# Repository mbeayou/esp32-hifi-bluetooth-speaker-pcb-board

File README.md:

# ESP32 HiFi Bluetooth Speaker PCB Board

This project showcases the design and assembly of a **HiFi Bluetooth speaker PCB board** based on the ESP32.  
It includes PCB layer visualization, the assembled board, and BLE schematics for reference.

## 📐 PCB Layers

## 🔧 Assembled PCB

## 📊 Schematics (BLE)

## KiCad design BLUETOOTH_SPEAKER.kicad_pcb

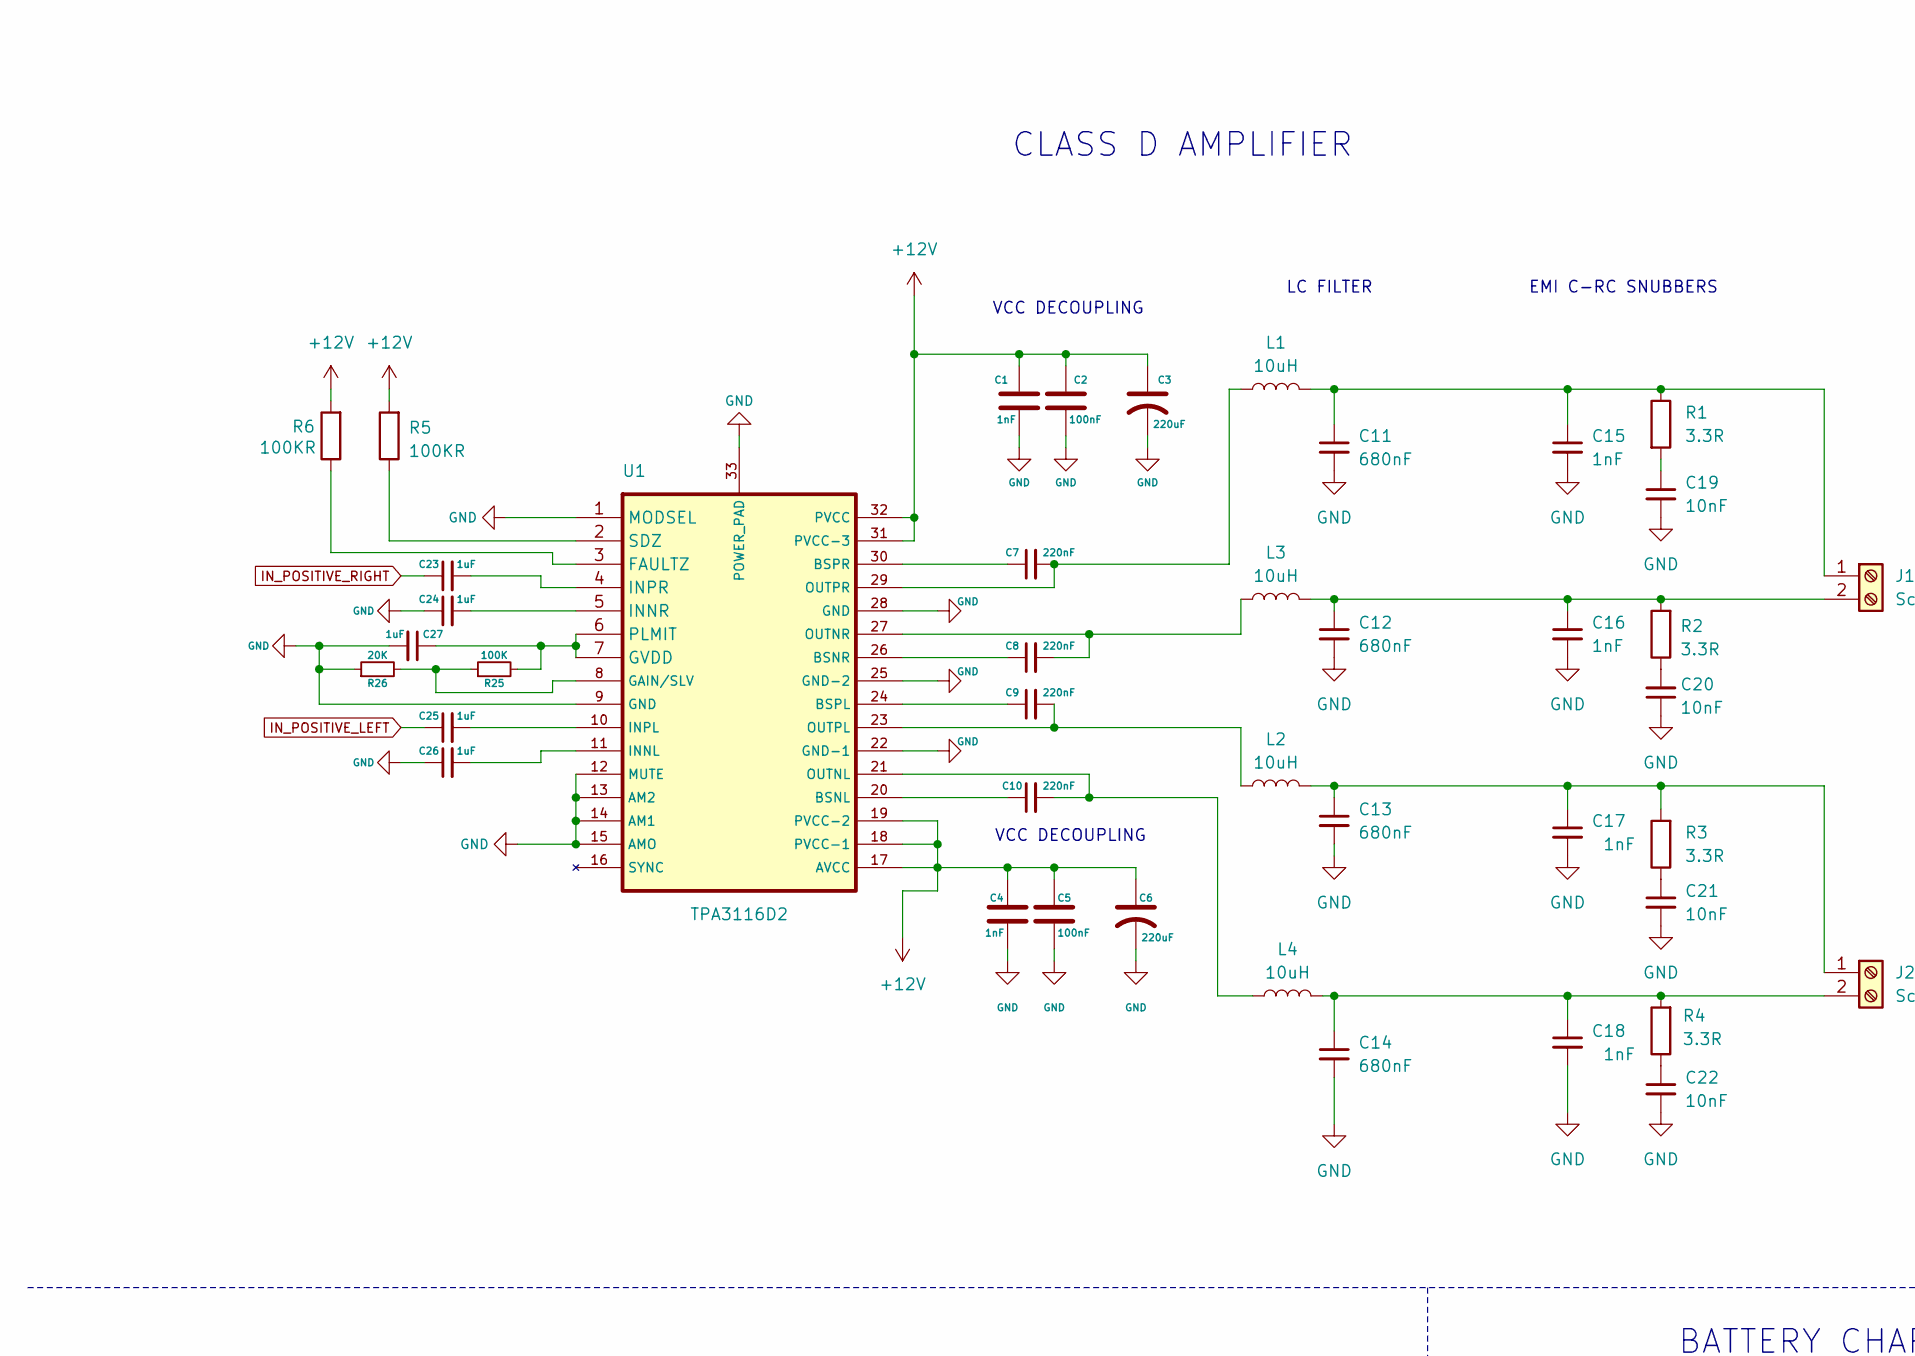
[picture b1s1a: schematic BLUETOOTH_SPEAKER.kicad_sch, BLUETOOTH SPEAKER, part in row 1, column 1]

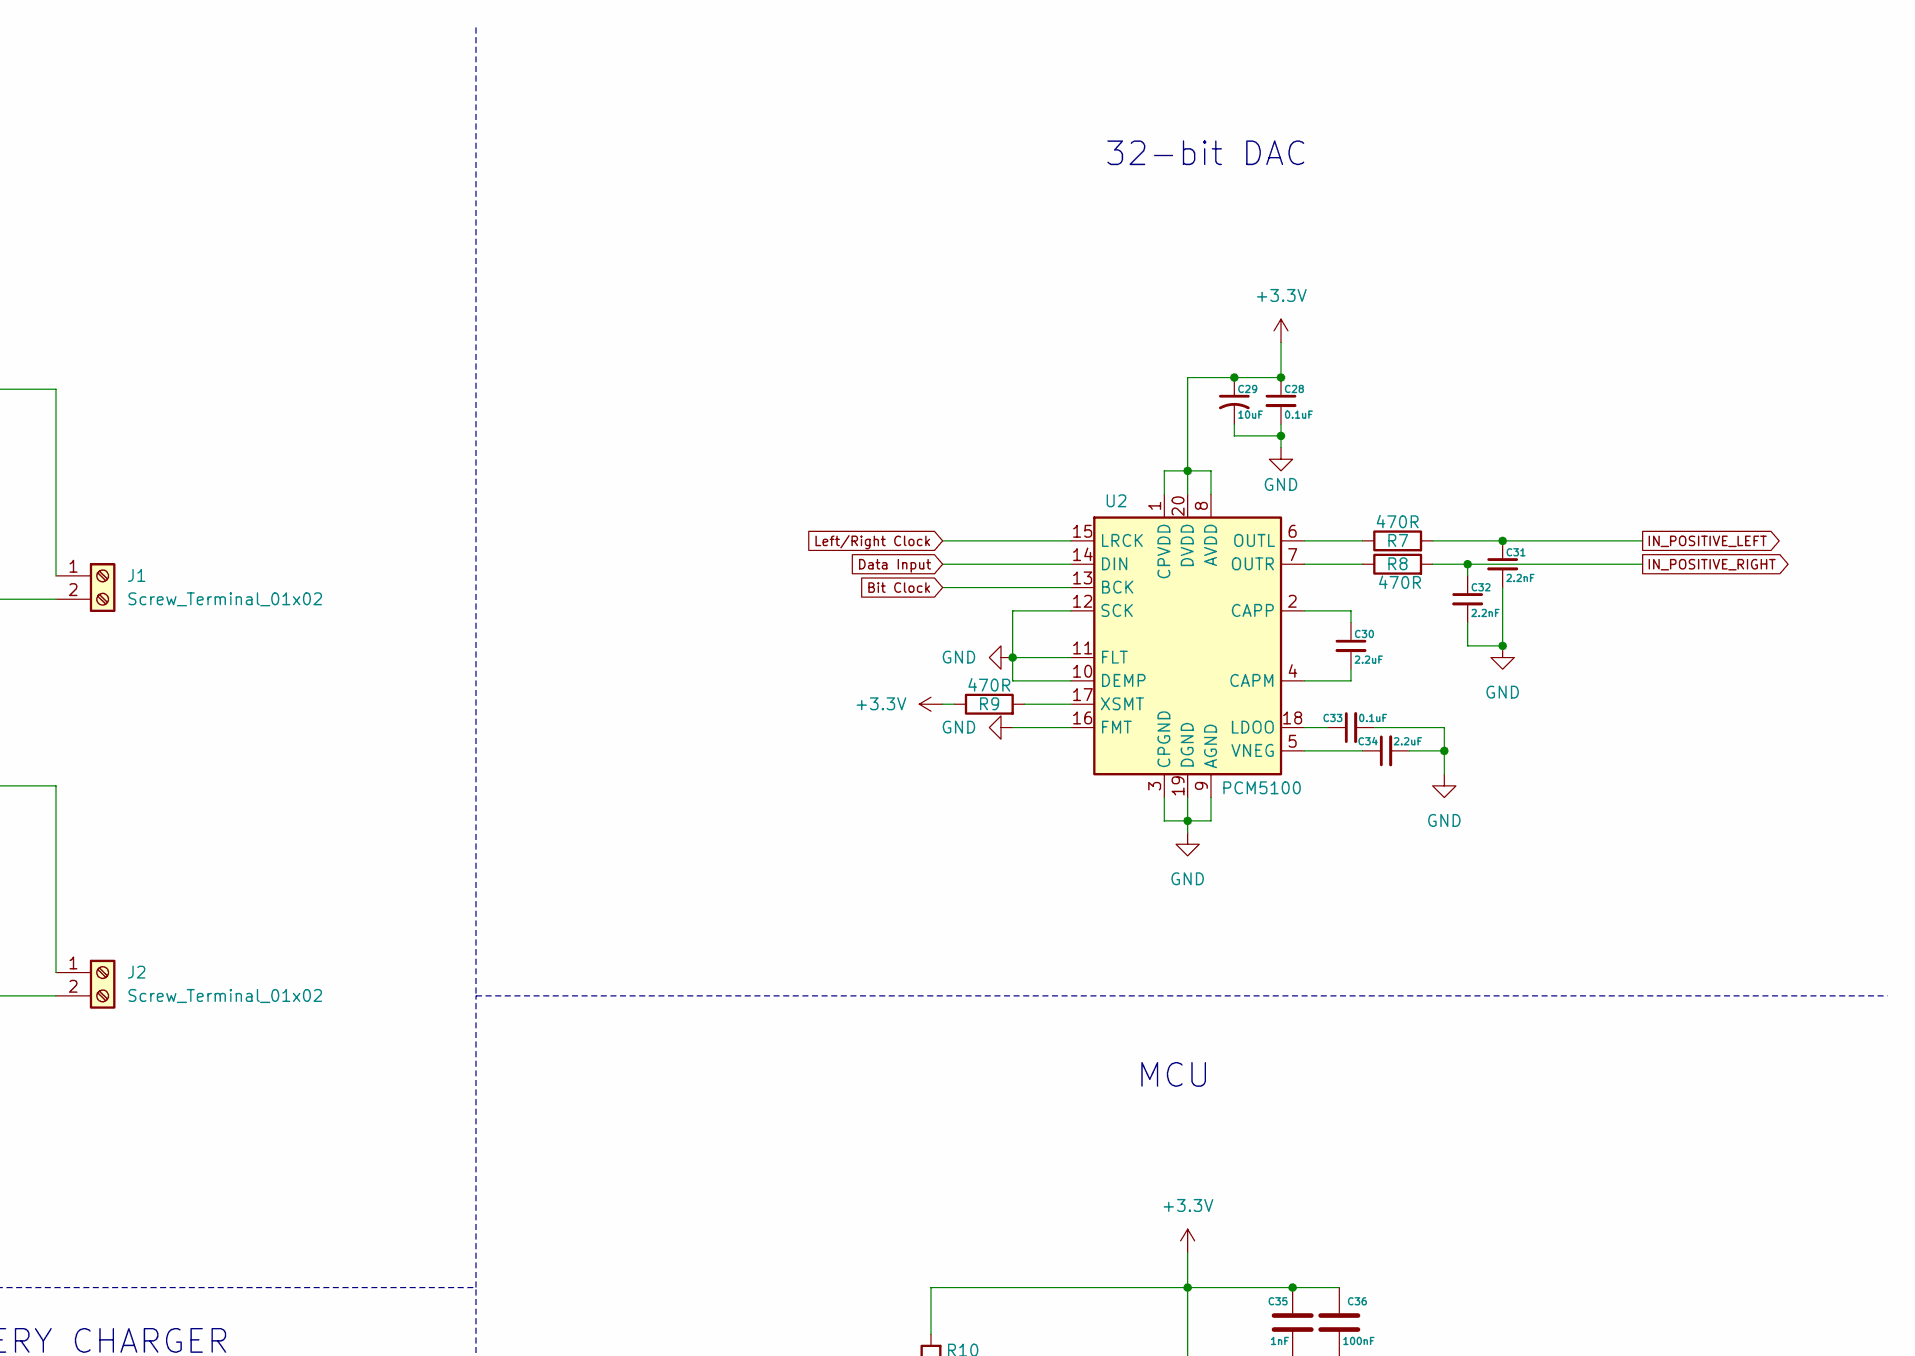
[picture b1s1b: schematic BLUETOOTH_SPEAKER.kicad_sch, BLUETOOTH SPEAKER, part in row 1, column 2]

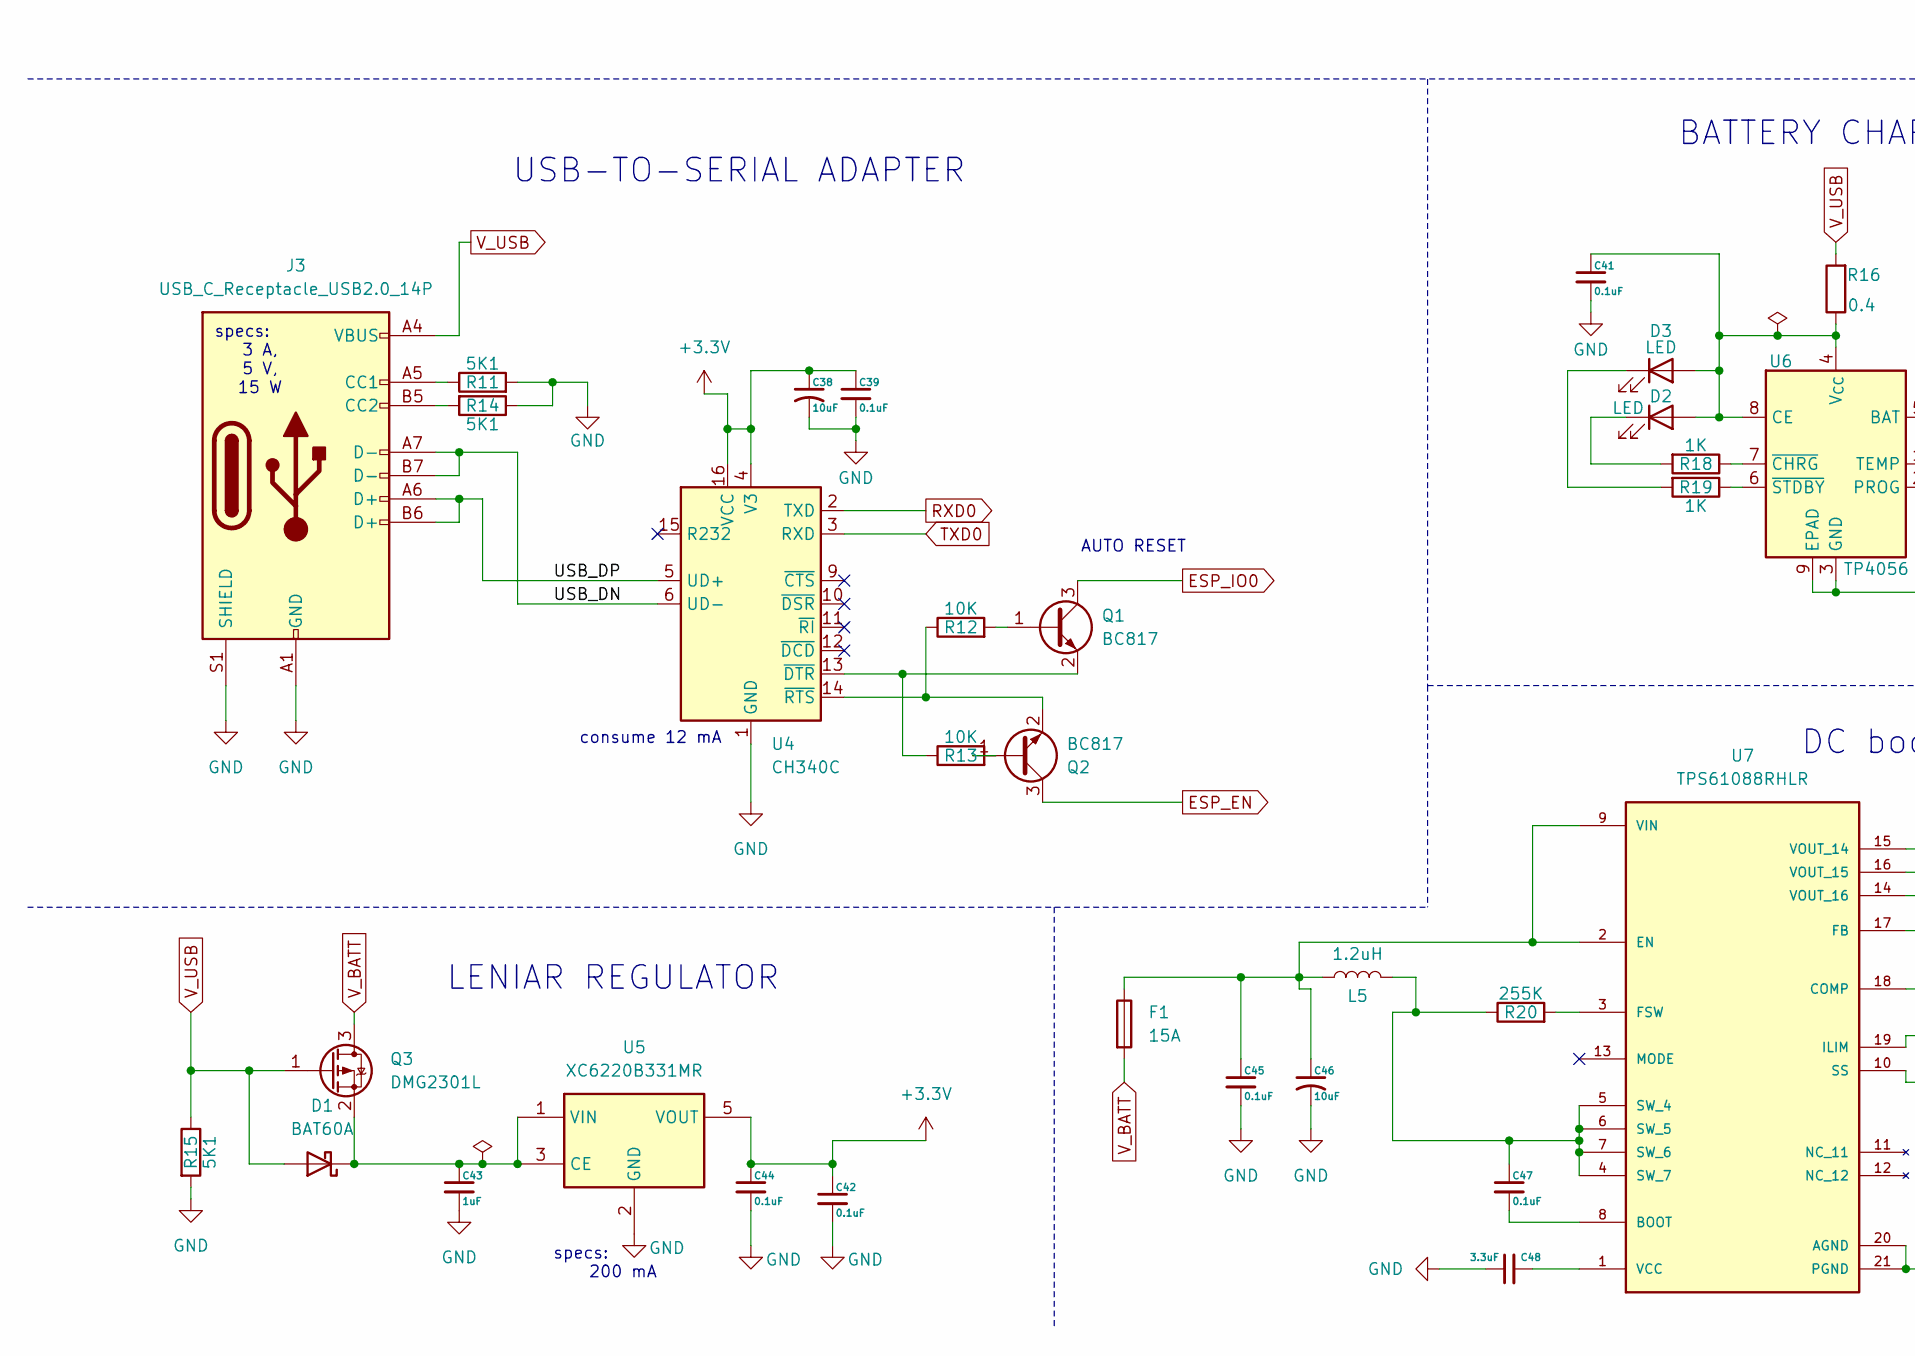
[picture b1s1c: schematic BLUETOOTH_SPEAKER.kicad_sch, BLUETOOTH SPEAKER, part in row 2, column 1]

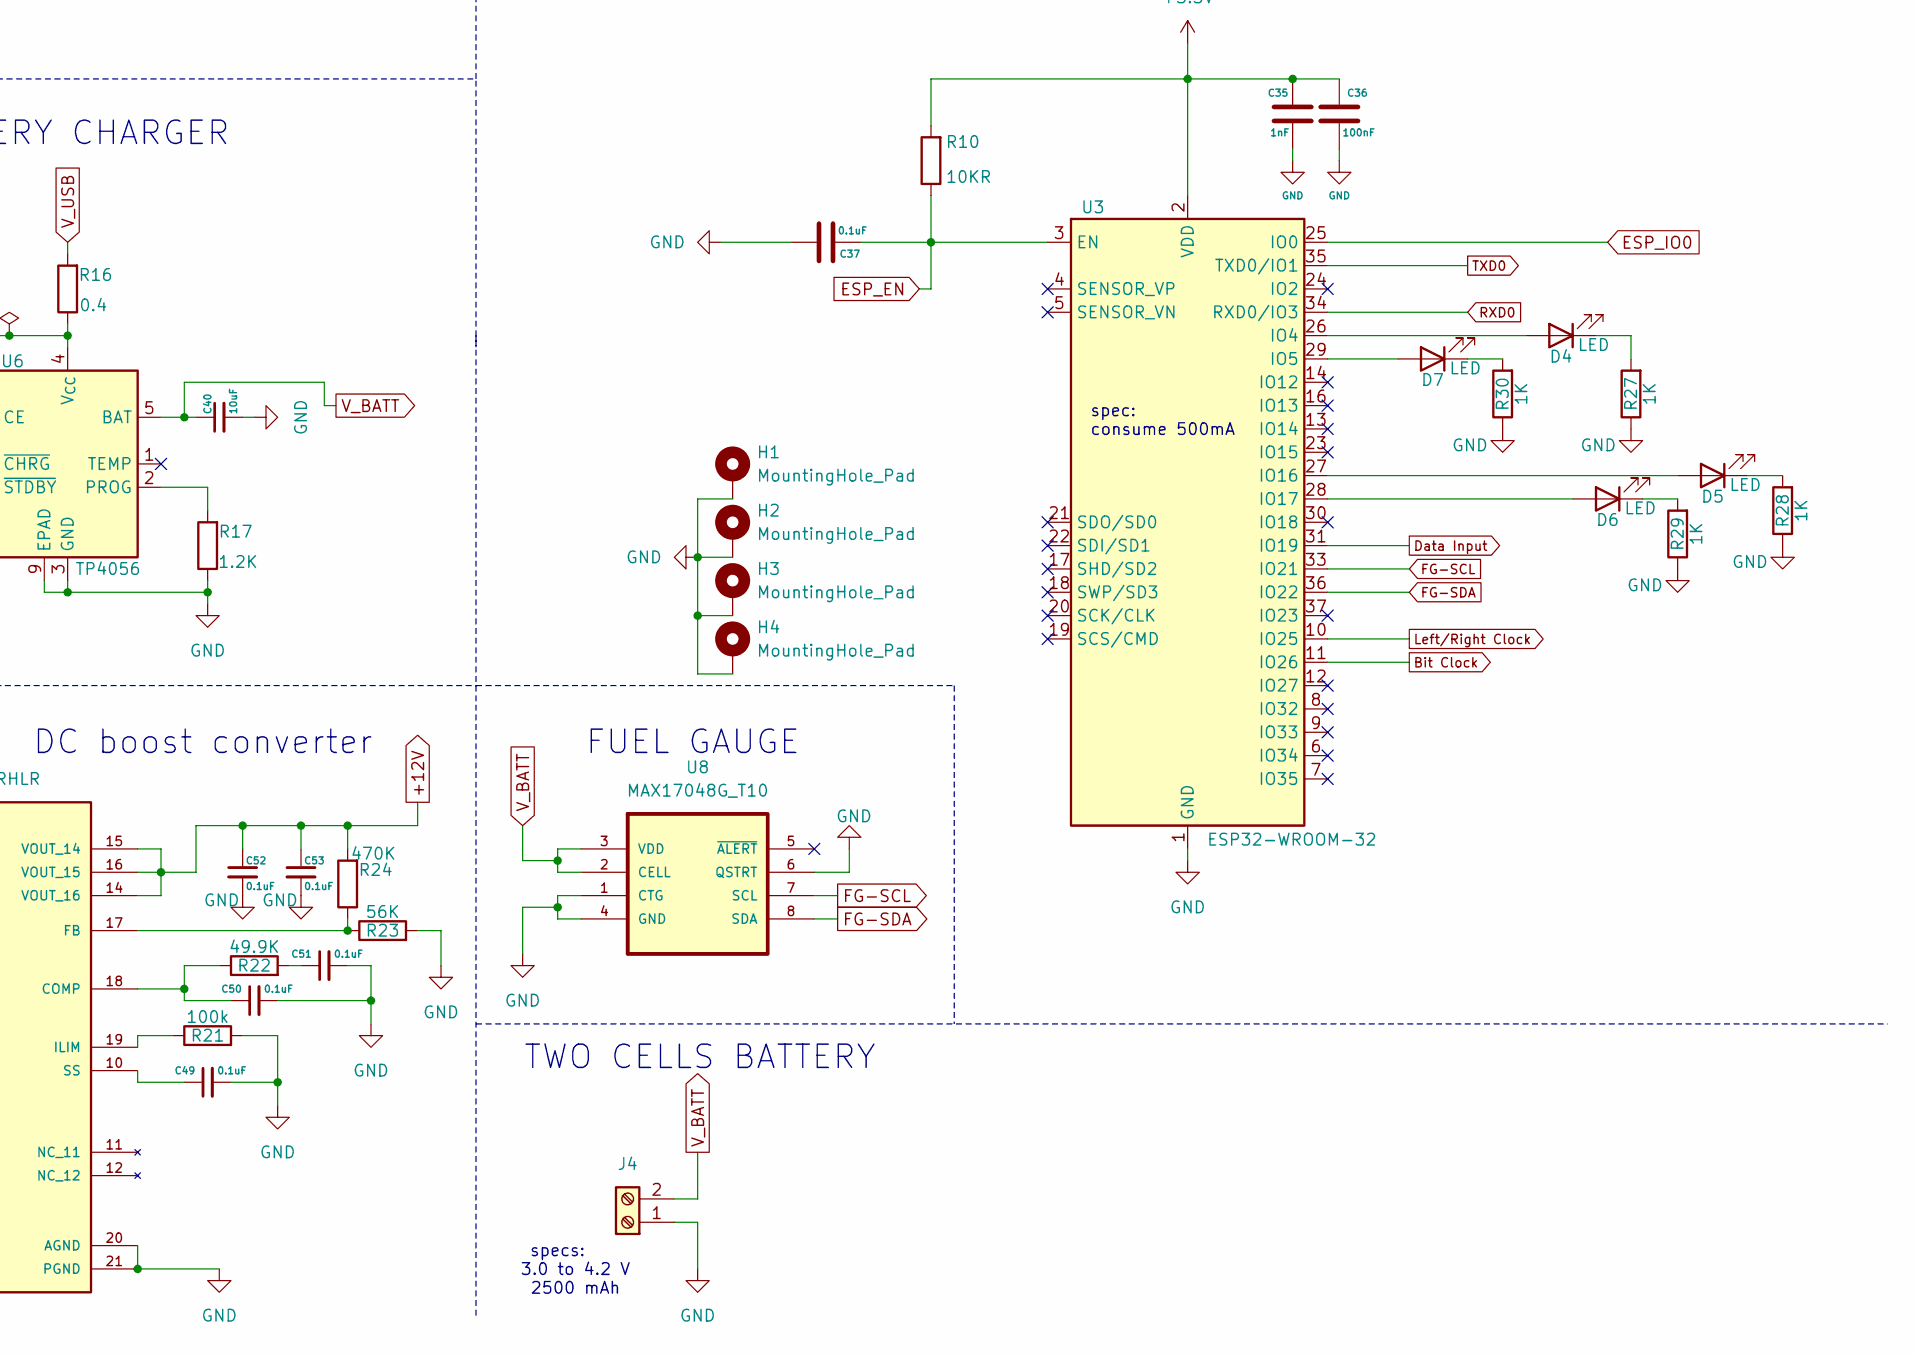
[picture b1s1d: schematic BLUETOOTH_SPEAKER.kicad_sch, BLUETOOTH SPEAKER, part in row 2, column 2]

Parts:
C1, C4, C15, C16, C17, C18, C35: 1nF; C_0603_1608Metric_Pad1.08x0.95mm_HandSolder
C2, C5, C36: 100nF; C_0805_2012Metric_Pad1.18x1.45mm_HandSolder
C3, C6: 220uF; C_1210_3225Metric_Pad1.33x2.70mm_HandSolder
C7, C8, C9, C10: 220nF; C_0805_2012Metric_Pad1.18x1.45mm_HandSolder
C11, C12, C13, C14: 680nF; C_0805_2012Metric_Pad1.18x1.45mm_HandSolder
C19, C20, C21, C22: 10nF; C_0603_1608Metric_Pad1.08x0.95mm_HandSolder
C23, C24, C25, C26, C43: 1uF; C_0805_2012Metric_Pad1.18x1.45mm_HandSolder
C27: 1uF; C_1206_3216Metric
C28, C33, C37, C39, C41, C42, C44, C45, C47, C49, C50, C51, C52, C53: 0.1uF; C_0805_2012Metric_Pad1.18x1.45mm_HandSolder
C29: 10uF; C_1206_3216Metric_Pad1.33x1.80mm_HandSolder
C30, C34: 2.2uF; C_0805_2012Metric_Pad1.18x1.45mm_HandSolder
C31, C32: 2.2nF; C_0603_1608Metric_Pad1.08x0.95mm_HandSolder
C38, C40, C46: 10uF; C_1210_3225Metric_Pad1.33x2.70mm_HandSolder
C48: 3.3uF; C_0805_2012Metric_Pad1.18x1.45mm_HandSolder
D1: BAT60A; D_SOD-323
D2, D3, D4, D5, D6, D7: LED; LED_1210_3225Metric_Pad1.42x2.65mm_HandSolder
F1: 15A; Fuseholder_Cylinder-6.3x32mm_Schurter_0031-8002_Horizontal_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
H1, H2, H3, H4: MountingHole_Pad; MountingHole_2.2mm_M2_Pad_Via
J1, J2: Screw_Terminal_01x02; JST_XH_S2B-XH-A-1_1x02_P2.50mm_Horizontal
J3: USB_C_Receptacle_USB2.0_14P; USB_C_Receptacle_Palconn_UTC16-G
J4: Screw_Terminal_01x02; JST_PH_B2B-PH-K_1x02_P2.00mm_Vertical
L1, L2, L3, L4: 10uH; WE-PD_1260
L5: 1.2uH; WE-PD_1260
Q1, Q2: BC817; SOT-23
Q3: DMG2301L; SOT-23
R1, R2, R3, R4: 3.3R; R_0603_1608Metric_Pad0.98x0.95mm_HandSolder
R5, R6: 100KR; R_1210_3225Metric_Pad1.30x2.65mm_HandSolder
R7, R8, R9: 470R; R_0805_2012Metric_Pad1.20x1.40mm_HandSolder
R10: 10KR; R_1210_3225Metric_Pad1.30x2.65mm_HandSolder
R11, R14, R15: 5K1; R_0805_2012Metric_Pad1.20x1.40mm_HandSolder
R12, R13: 10K; R_1210_3225Metric_Pad1.30x2.65mm_HandSolder
R16: 0.4; R_0805_2012Metric_Pad1.20x1.40mm_HandSolder
R17: 1.2K; R_0805_2012Metric_Pad1.20x1.40mm_HandSolder
R18, R19, R27, R28, R29, R30: 1K; R_0805_2012Metric_Pad1.20x1.40mm_HandSolder
R20: 255K; R_1210_3225Metric_Pad1.30x2.65mm_HandSolder
R21: 100k; R_1210_3225Metric_Pad1.30x2.65mm_HandSolder
R22: 49.9K; R_1210_3225Metric_Pad1.30x2.65mm_HandSolder
R23: 56K; R_1210_3225Metric_Pad1.30x2.65mm_HandSolder
R24: 470K; R_1210_3225Metric_Pad1.30x2.65mm_HandSolder
R25: 100K; R_0402_1005Metric
R26: 20K; R_0402_1005Metric
U1: TPA3116D2; SOP65P810X115-33N
U2: PCM5100; TSSOP-20_4.4x6.5mm_P0.65mm
U3: ESP32-WROOM-32
U4: CH340C; SOIC-16_3.9x9.9mm_P1.27mm
U5: XC6220B331MR; SOT-23-5
U6: TP4056; SOIC-8-1EP_3.9x4.9mm_P1.27mm_EP2.41x3.3mm_ThermalVias
U7: TPS61088RHLR; VQFN-20; PARTREV 4219071/A 05/2017
U8: MAX17048G_T10; SON50P200X200X80-9N

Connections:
+3.3V: C28.1, C29.1, C35.1, C36.1, C38.1, C39.1, C42.1, C44.1, R9.1, R10.2, U2.1 (CPVDD), U2.8 (AVDD), U2.20 (DVDD), U3.2 (VDD), U4.4 (V3), U4.16 (VCC), U5.5 (VOUT)
+12V: C1.1, C2.1, C3.1, C4.1, C5.1, C6.1, C52.1, C53.1, R5.2, R6.2, R24.2, U1.17 (AVCC), U1.18 (PVCC-1), U1.19 (PVCC-2), U1.31 (PVCC-3), U1.32 (PVCC), U7.14 (VOUT_16), U7.15 (VOUT_14), U7.16 (VOUT_15)
/USB_DN: J3.A7 (D-), J3.B7 (D-), U4.6 (UD-)
/USB_DP: J3.A6 (D+), J3.B6 (D+), U4.5 (UD+)
Bit Clock: U2.13 (BCK), U3.11 (IO26)
Data Input: U2.14 (DIN), U3.31 (IO19)
ESP_EN: C37.2, Q2.3 (C), R10.1, U3.3 (EN)
ESP_IO0: Q1.3 (C), U3.25 (IO0)
FG-SCL: U3.33 (IO21), U8.7 (SCL)
FG-SDA: U3.36 (IO22), U8.8 (SDA)
GND: C1.2, C2.2, C3.2, C4.2, C5.2, C6.2, C11.2, C12.2, C13.2, C14.2, C15.2, C16.2, C17.2, C18.2, C19.2, C20.1, C21.2, C22.2, C24.1, C26.1, C27.2, C28.2, C29.2, C31.2, C32.2, C33.2, C34.2, C35.2, C36.2, C37.1, C38.2, C39.2, C40.2, C41.2, C42.2, C43.2, C44.2, C45.2, C46.2, C48.1, C49.2, C50.2, C51.2, C52.2, C53.2, H1.1, H2.1, H3.1, H4.1, J3.A1 (GND), J3.A12 (GND), J3.B1 (GND), J3.B12 (GND), J3.S1 (SHIELD), J4.1, R11.2, R14.1, R15.2, R17.1, R21.2, R23.2, R26.1, R27.1, R28.1, R29.1, R30.1, U1.1 (MODSEL), U1.9 (GND), U1.12 (MUTE), U1.13 (AM2), U1.14 (AM1), U1.15 (AMO), U1.22 (GND-1), U1.25 (GND-2), U1.28 (GND), U1.33 (POWER_PAD), U2.3 (CPGND), U2.9 (AGND), U2.10 (DEMP), U2.11 (FLT), U2.12 (SCK), U2.16 (FMT), U2.19 (DGND), U3.1 (GND), U3.15 (GND), U3.38 (GND), U3.39 (GND), U4.1 (GND), U5.2 (GND), U6.3 (GND), U6.9 (EPAD), U7.20 (AGND), U7.21 (PGND), U7.22 (PGND), U7.23 (PGND), U7.24 (PGND), U7.25 (PGND), U7.26 (PGND), U7.27 (PGND), U7.28 (PGND), U7.29 (PGND), U8.1 (CTG), U8.4 (GND), U8.6 (QSTRT)
IN_POSITIVE_LEFT: C25.1, C31.1, R7.2
IN_POSITIVE_RIGHT: C23.1, C32.1, R8.2
Left/Right Clock: U2.15 (LRCK), U3.10 (IO25)
unnamed: C19.1, R1.2
unnamed: C20.2, R2.1
unnamed: C21.1, R3.1
unnamed: C22.1, R4.1
unnamed: C51.1, R22.2
unnamed: C43.1, D1.1 (K), Q3.2 (S), U5.1 (VIN), U5.3 (CE)
unnamed: C41.1, D2.2 (A), D3.2 (A), R16.1, U6.4 (V_{CC}), U6.8 (CE)
unnamed: D2.1 (K), R18.2
unnamed: D3.1 (K), R19.2
unnamed: D4.2 (A), U3.26 (IO4)
unnamed: D4.1 (K), R27.2
unnamed: D5.2 (A), U3.27 (IO16)
unnamed: D5.1 (K), R28.2
unnamed: D6.2 (A), U3.28 (IO17)
unnamed: D6.1 (K), R29.2
unnamed: D7.2 (A), U3.29 (IO5)
unnamed: D7.1 (K), R30.2
unnamed: C11.1, C15.1, J1.1, L1.2, R1.1
unnamed: C12.1, C16.1, J1.2, L3.2, R2.2
unnamed: C13.1, C17.1, J2.1, L2.2, R3.2
unnamed: C14.1, C18.1, J2.2, L4.2, R4.2
unnamed: J3.A5 (CC1), R11.1
unnamed: J3.B5 (CC2), R14.2
unnamed: Q1.1 (B), R12.2
unnamed: Q1.2 (E), R13.1, U4.13 (~DTR)
unnamed: Q2.1 (B), R13.2
unnamed: Q2.2 (E), R12.1, U4.14 (~RTS)
unnamed: C10.1, U1.20 (BSNL)
unnamed: C8.1, U1.26 (BSNR)
unnamed: C9.1, U1.24 (BSPL)
unnamed: C7.1, U1.30 (BSPR)
unnamed: R6.1, U1.3 (FAULTZ)
unnamed: R25.1, R26.2, U1.8 (GAIN/SLV)
unnamed: C27.1, R25.2, U1.6 (PLMIT), U1.7 (GVDD)
unnamed: C26.2, U1.11 (INNL)
unnamed: C24.2, U1.5 (INNR)
unnamed: C25.2, U1.10 (INPL)
unnamed: C23.2, U1.4 (INPR)
unnamed: C10.2, L4.1, U1.21 (OUTNL)
unnamed: C8.2, L3.1, U1.27 (OUTNR)
unnamed: C9.2, L2.1, U1.23 (OUTPL)
unnamed: C7.2, L1.1, U1.29 (OUTPR)
unnamed: R5.1, U1.2 (SDZ)
unnamed: C30.2, U2.4 (CAPM)
unnamed: C30.1, U2.2 (CAPP)
unnamed: C33.1, U2.18 (LDOO)
unnamed: R7.1, U2.6 (OUTL)
unnamed: R8.1, U2.7 (OUTR)
unnamed: C34.1, U2.5 (VNEG)
unnamed: R9.2, U2.17 (XSMT)
unnamed: R17.2, U6.2 (PROG)
unnamed: R18.1, U6.7 (~CHRG)
unnamed: R19.1, U6.6 (~STDBY)
unnamed: C47.2, U7.8 (BOOT)
unnamed: C50.1, R22.1, U7.18 (COMP)
unnamed: C45.1, C46.1, F1.1, L5.1, U7.2 (EN), U7.9 (VIN)
unnamed: R23.1, R24.1, U7.17 (FB)
unnamed: R20.2, U7.3 (FSW)
unnamed: R21.1, U7.19 (ILIM)
unnamed: C49.1, U7.10 (SS)
unnamed: C47.1, L5.2, R20.1, U7.4 (SW_7), U7.5 (SW_4), U7.6 (SW_5), U7.7 (SW_6)
unnamed: C48.2, U7.1 (VCC)
RXD0: U3.34 (RXD0/IO3), U4.2 (TXD)
TXD0: U3.35 (TXD0/IO1), U4.3 (RXD)
V_BATT: C40.1, F1.2, J4.2, Q3.3 (D), U6.5 (BAT), U8.2 (CELL), U8.3 (VDD)
V_USB: D1.2 (A), J3.A4 (VBUS), J3.A9 (VBUS), J3.B4 (VBUS), J3.B9 (VBUS), Q3.1 (G), R15.1, R16.2

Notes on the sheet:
consume 12 mA
BATTERY CHARGER
VCC DECOUPLING
specs: 3 A, 5 V, 15 W
spec: consume 500mA
AUTO RESET
DC boost converter
MCU
specs: 3.0 to 4.2 V 2500 mAh
FUEL GAUGE
EMI C-RC SNUBBERS
CLASS D AMPLIFIER
TWO CELLS BATTERY
LC FILTER
LENIAR REGULATOR
USB-TO-SERIAL ADAPTER
32-bit DAC
specs: 200 mA

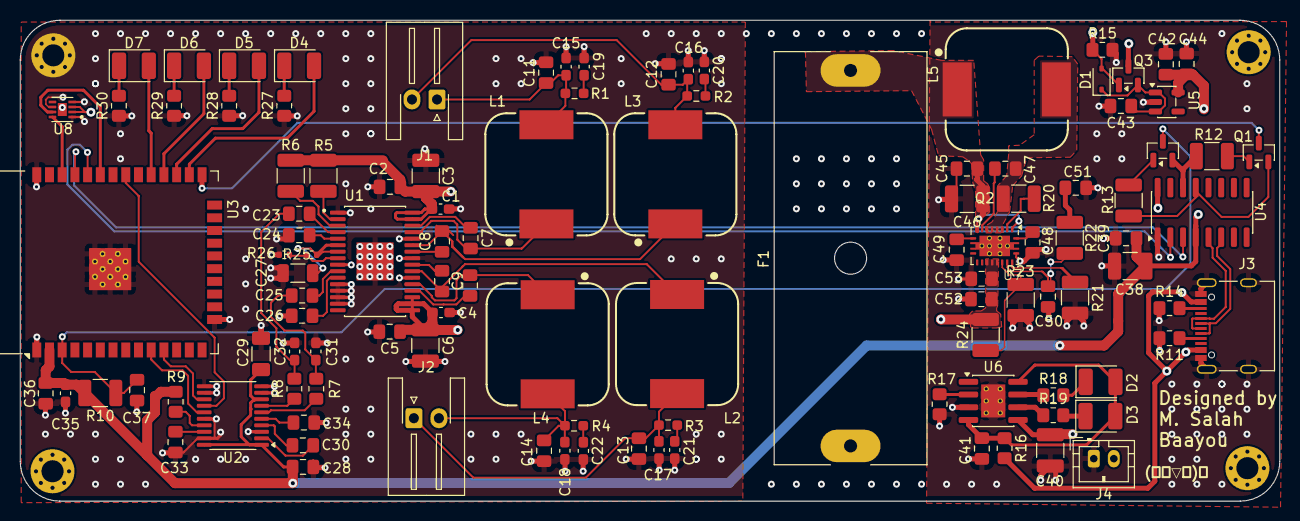
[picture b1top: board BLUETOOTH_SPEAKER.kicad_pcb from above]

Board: 4 copper layers, 125.8 x 48.0 mm, 115 parts (0 on the bottom side), 80 nets.

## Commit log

2025-12-25 Initialize README with project details and visuals
    Added project overview and images for PCB design.
